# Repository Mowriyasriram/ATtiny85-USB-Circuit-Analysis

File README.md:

# ATtiny85-USB-Circuit-Analysis
Open-source KiCAD 7 PCB project for a USB-enabled ATtiny85 Digispark-compatible board. Includes schematic, custom symbols, footprints, PCB layouts, and Gerber's for easy USB microcontroller prototyping and learning modern PCB design workflows.

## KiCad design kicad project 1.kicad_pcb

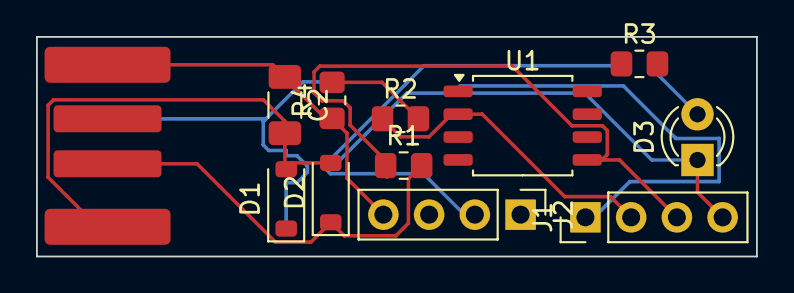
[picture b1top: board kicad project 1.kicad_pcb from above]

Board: 2 copper layers, 40.0 x 12.2 mm, 12 parts (0 on the bottom side), 9 nets.

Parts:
C2: 100n; C_1206_3216Metric_Pad1.33x1.80mm_HandSolder
D1, D2: 3v6; D_SOD-123
D3: LED; LED_D3.0mm_IRGrey
J1: S08-1-4; PinHeader_1x04_P2.54mm_Vertical
J2: SO8-5-8; PinHeader_1x04_P2.54mm_Vertical
R1, R2: 68R; R_0805_2012Metric_Pad1.20x1.40mm_HandSolder
R3: 330R; R_0805_2012Metric_Pad1.20x1.40mm_HandSolder
R4: 1k5; R_0805_2012Metric_Pad1.20x1.40mm_HandSolder
U1: ATtiny85-20M; SOIC-8_5.3x5.3mm_P1.27mm
U2: USB footprint

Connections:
+5V: C2.1, J2.4, R4.1, U2.1 (Vcc)
GND: C2.2, D1.2 (A), D2.2 (A), D3.1 (K), J1.4, U1.8 (GND), U2.4 (GND)
unnamed: D1.1 (K), R2.2, R4.2, U2.2 (D+)
unnamed: D2.1 (K), R1.2, U2.3 (D-)
unnamed: D3.2 (A), R3.2
unnamed: J1.1, U1.1 (~RESET/PB5)
unnamed: J1.2, R2.1, U1.2 (XTAL1/PB3)
unnamed: J1.3, R1.1, U1.5 (XTAL2/PB4)
unnamed: J2.2, R3.1
